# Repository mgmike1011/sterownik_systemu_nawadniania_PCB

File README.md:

# sterownik_systemu_nawadniania_PCB
Projekt płytki drukowanej sterownika systemu nawadaniania w oparciu o STM32

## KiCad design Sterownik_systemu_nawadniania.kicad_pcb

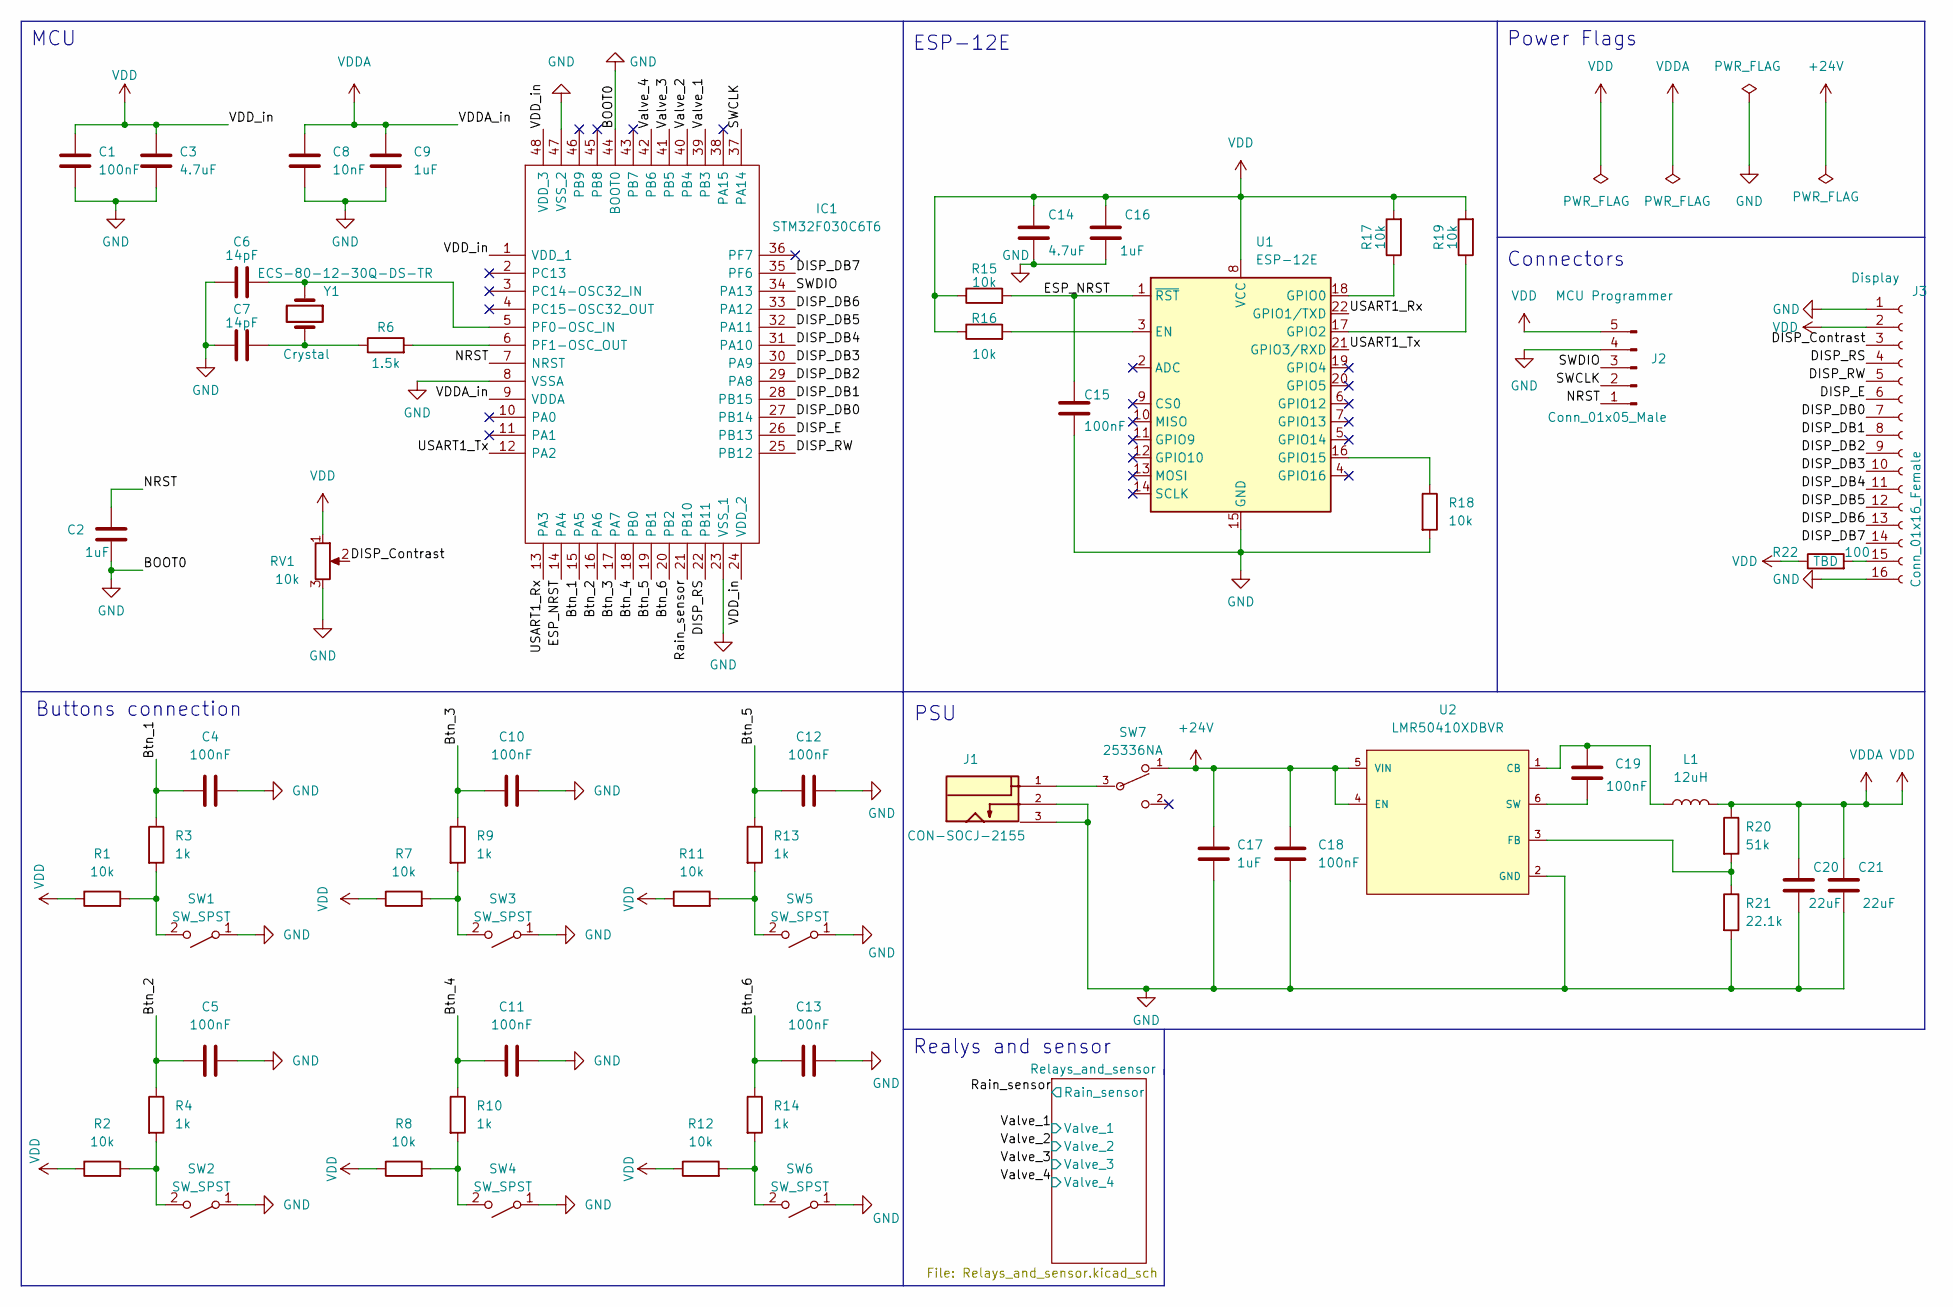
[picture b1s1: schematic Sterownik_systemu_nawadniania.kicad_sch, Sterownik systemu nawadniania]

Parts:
C1, C4, C5, C10, C11, C12, C13, C15, C18, C19: 100nF; C_0603_1608Metric
C2, C9, C16, C17: 1uF; C_0603_1608Metric
C3, C14: 4.7uF; C_0603_1608Metric
C6, C7: 14pF; C_0402_1005Metric
C8: 10nF; C_0603_1608Metric
C20, C21: 22uF; C_2220_5650Metric
IC1: STM32F030C6T6; QFP50P900X900X160-48N; Mouser Part Number 511-STM32F030C6T6
J1: CON-SOCJ-2155; GRAVITECH_CON-SOCJ-2155; PARTREV NA
J2: Conn_01x05_Male; PinHeader_1x05_P2.54mm_Vertical
J3: Conn_01x16_Female; PinSocket_1x16_P2.54mm_Vertical
L1: 12uH; RLB0712-120KL
R1, R2, R7, R8, R11, R12, R15, R16, R17, R18, R19: 10k; R_0603_1608Metric
R3, R4, R9, R10, R13, R14: 1k; R_0603_1608Metric
R6: 1.5k; R_0603_1608Metric
R20: 51k; R_0603_1608Metric
R21: 22.1k; R_0603_1608Metric
R22: 100; R_0603_1608Metric
RV1: 10k; TRIM_3362P-1-103LF
SW1, SW2, SW3, SW4, SW5, SW6: SW_SPST; 430156043736_AM
SW7: 25336NA; Apem_Inc.-25336NA-MFG; voltage rating DC 30V; mouser part number 642-25336NA; digikey description SWITCH SLIDE SPDT 4A 125V
U1: ESP-12E
U2: LMR50410XDBVR; Texas_Instruments-DBV0006A-0-0-MFG; output voltage 1-28V; mouser part number 595-LMR50410XDBVR; digikey description SIMPLE SWITCHER 4-V TO 36-V, 1-A
Y1: Crystal; XTAL_ECS-80-18-30-JGN-TR

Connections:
/Btn_1: C4.1, IC1.15 (PA5), R3.1
/Btn_2: C5.1, IC1.16 (PA6), R4.1
/Btn_3: C10.1, IC1.17 (PA7), R9.1
/Btn_4: C11.1, IC1.18 (PB0), R10.1
/Btn_5: C12.1, IC1.19 (PB1), R13.1
/Btn_6: C13.1, IC1.20 (PB2), R14.1
/DISP_Contrast: J3.3, RV1.2
/DISP_DB0: IC1.27 (PB14), J3.7
/DISP_DB1: IC1.28 (PB15), J3.8
/DISP_DB2: IC1.29 (PA8), J3.9
/DISP_DB3: IC1.30 (PA9), J3.10
/DISP_DB4: IC1.31 (PA10), J3.11
/DISP_DB5: IC1.32 (PA11), J3.12
/DISP_DB6: IC1.33 (PA12), J3.13
/DISP_DB7: IC1.35 (PF6), J3.14
/DISP_E: IC1.26 (PB13), J3.6
/DISP_RS: IC1.22 (PB11), J3.4
/DISP_RW: IC1.25 (PB12), J3.5
/ESP_NRST: C15.1, IC1.14 (PA4), R15.2, U1.1 (~RST)
/NRST: C2.1, IC1.7 (NRST), J2.1
/Rain_sensor: IC1.21 (PB10); also elsewhere on the board
/SWCLK: IC1.37 (PA14), J2.2
/SWDIO: IC1.34 (PA13), J2.3
/USART1_Rx: IC1.13 (PA3), U1.22 (GPIO1/TXD)
/USART1_Tx: IC1.12 (PA2), U1.21 (GPIO3/RXD)
/Valve_1: IC1.39 (PB3); also elsewhere on the board
/Valve_2: IC1.40 (PB4); also elsewhere on the board
/Valve_3: IC1.41 (PB5); also elsewhere on the board
/Valve_4: IC1.42 (PB6); also elsewhere on the board
GND: C1.2, C2.2, C3.2, C4.2, C5.2, C6.1, C7.1, C8.2, C9.2, C10.2, C11.2, C12.2, C13.2, C14.2, C15.2, C16.2, C17.2, C18.2, C20.2, C21.2, IC1.8 (VSSA), IC1.23 (VSS_1), IC1.44 (BOOT0), IC1.47 (VSS_2), J1.2, J1.3, J2.4, J3.1, J3.16, R18.2, R21.2, RV1.3, SW1.1 (A), SW2.1 (A), SW3.1 (A), SW4.1 (A), SW5.1 (A), SW6.1 (A), U1.15 (GND), U2.2 (GND); also elsewhere on the board
unnamed: C6.2, IC1.5 (PF0-OSC_IN), Y1.1
unnamed: C7.2, R6.1, Y1.2
unnamed: C19.1, L1.1, U2.1 (CB)
unnamed: C19.2, U2.6 (SW)
unnamed: IC1.6 (PF1-OSC_OUT), R6.2
unnamed: J1.1, SW7.3 (Common)
unnamed: J3.15, R22.2
unnamed: R1.2, R3.2, SW1.2 (B)
unnamed: R2.2, R4.2, SW2.2 (B)
unnamed: R7.2, R9.2, SW3.2 (B)
unnamed: R8.2, R10.2, SW4.2 (B)
unnamed: R11.2, R13.2, SW5.2 (B)
unnamed: R12.2, R14.2, SW6.2 (B)
unnamed: R16.2, U1.3 (EN)
unnamed: R17.1, U1.18 (GPIO0)
unnamed: R18.1, U1.16 (GPIO15)
unnamed: R19.1, U1.17 (GPIO2)
unnamed: R20.2, R21.1, U2.3 (FB)
VDD: C1.1, C3.1, C8.1, C9.1, C14.1, C16.1, C20.1, C21.1, IC1.1 (VDD_1), IC1.9 (VDDA), IC1.24 (VDD_2), IC1.48 (VDD_3), J2.5, J3.2, L1.2, R1.1, R2.1, R7.1, R8.1, R11.1, R12.1, R15.1, R16.1, R17.2, R19.2, R20.1, R22.1, RV1.1, U1.8 (VCC); also elsewhere on the board

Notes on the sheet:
Realys and sensor
PSU
MCU
Buttons connection
Connectors
ESP-12E
Power Flags

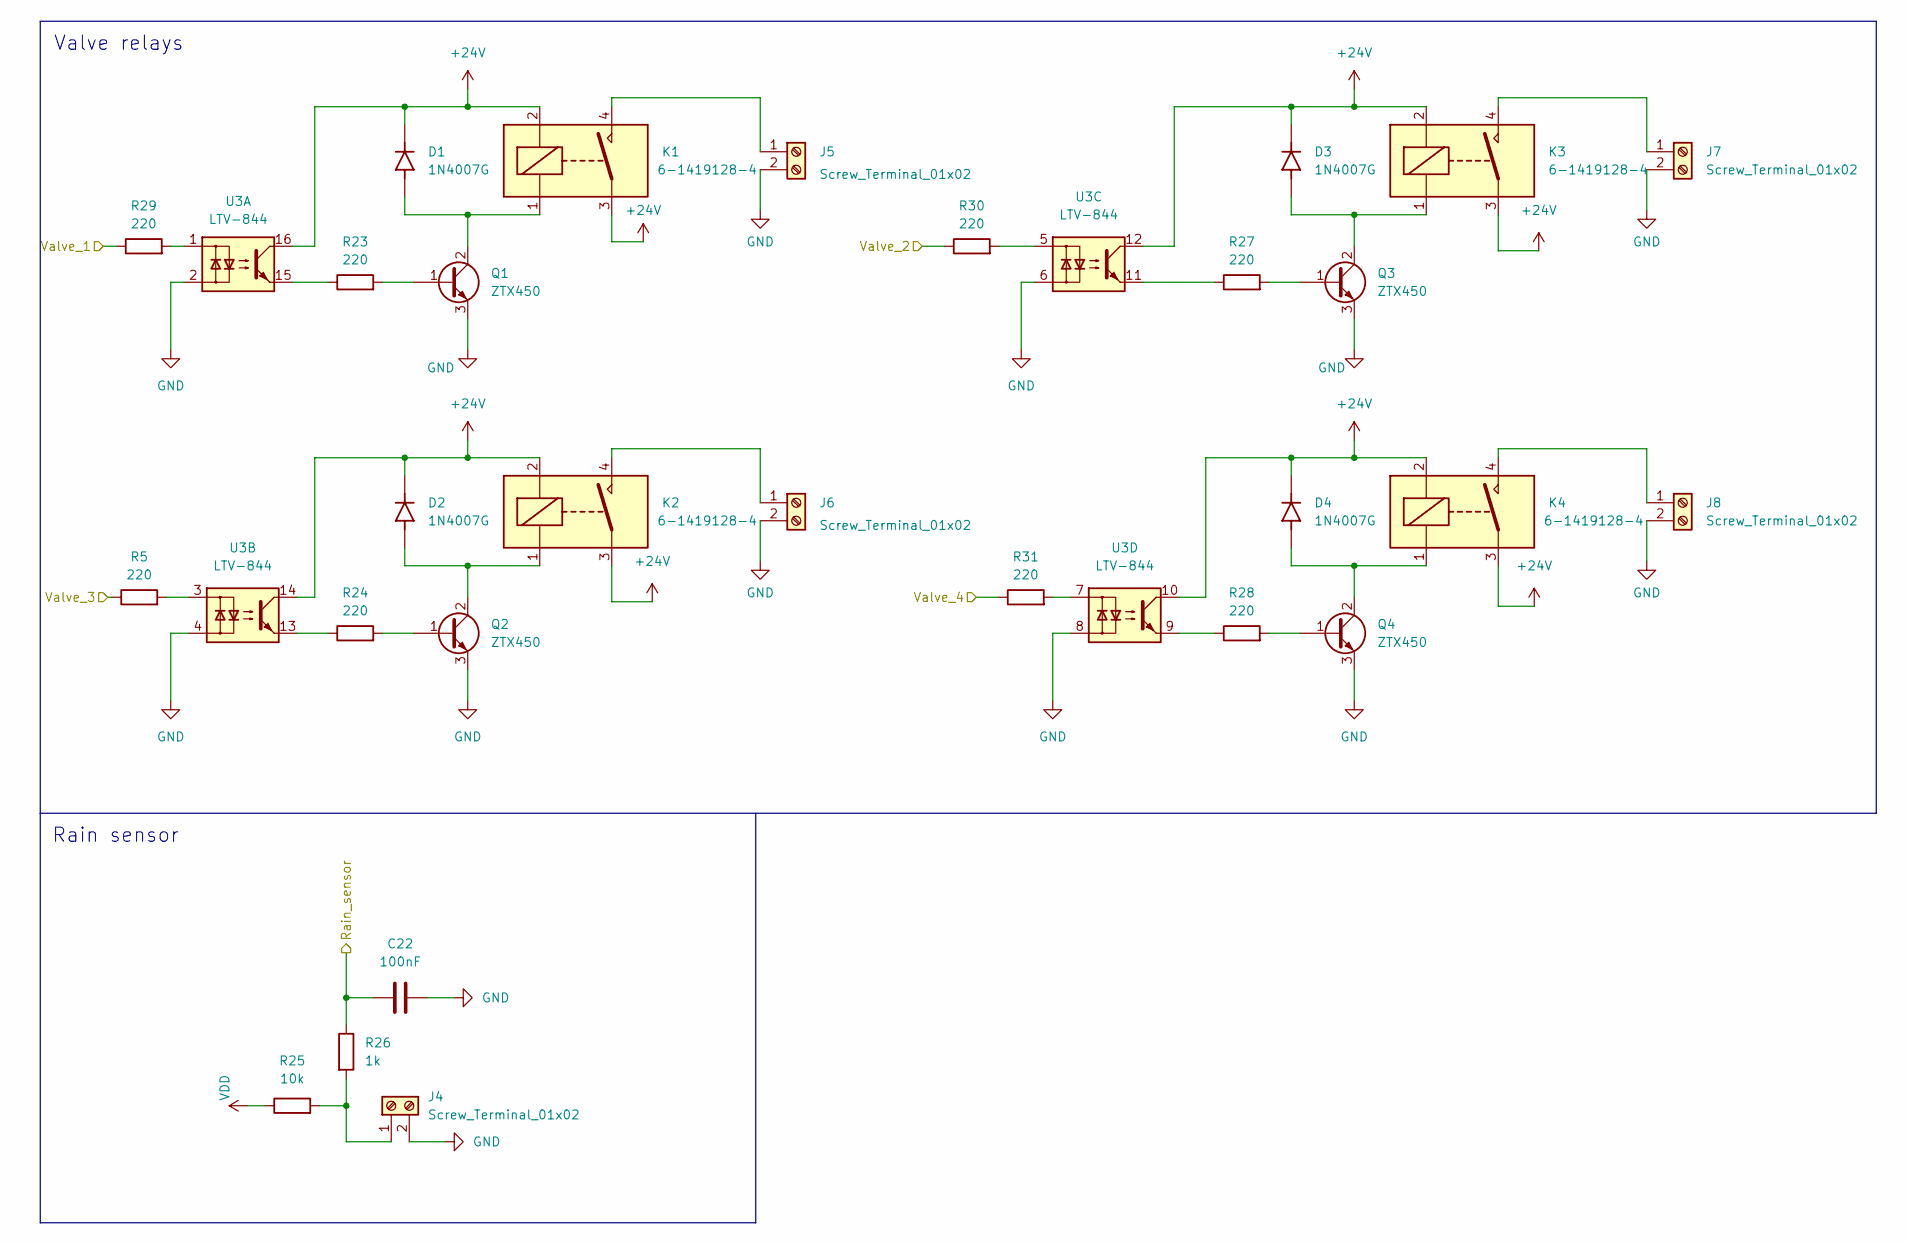
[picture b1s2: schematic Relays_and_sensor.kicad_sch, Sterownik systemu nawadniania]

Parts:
C22: 100nF; C_0603_1608Metric
D1, D2, D3, D4: 1N4007G; DIOAD1036W78L470D235; PARTREV P2104
J4, J5, J6, J7, J8: Screw_Terminal_01x02; TerminalBlock_bornier-2_P5.08mm
K1, K2, K3, K4: 6-1419128-4; OJ_OJE
Q1, Q2, Q3, Q4: ZTX450; TO92250P510H770-3
R5, R23, R24, R27, R28, R29, R30, R31: 220; R_0603_1608Metric
R25: 10k; R_0603_1608Metric
R26: 1k; R_0603_1608Metric
U3: LTV-844; DIP-16_W7.62mm

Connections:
/Rain_sensor: C22.1, R26.1; also elsewhere on the board
/Valve_1: R29.1; also elsewhere on the board
/Valve_2: R30.1; also elsewhere on the board
/Valve_3: R5.1; also elsewhere on the board
/Valve_4: R31.1; also elsewhere on the board
GND: C22.2, J4.2, J5.2, J6.2, J7.2, J8.2, Q1.3 (E), Q2.3 (E), Q3.3 (E), Q4.3 (E), U3.2, U3.4, U3.6, U3.8; also elsewhere on the board
unnamed: D1.A, K1.1, Q1.2 (C)
unnamed: D2.A, K2.1, Q2.2 (C)
unnamed: D3.A, K3.1, Q3.2 (C)
unnamed: D4.A, K4.1, Q4.2 (C)
unnamed: J4.1, R25.2, R26.2
unnamed: J5.1, K1.4
unnamed: J6.1, K2.4
unnamed: J7.1, K3.4
unnamed: J8.1, K4.4
unnamed: Q1.1 (B), R23.2
unnamed: Q2.1 (B), R24.2
unnamed: Q3.1 (B), R27.2
unnamed: Q4.1 (B), R28.2
unnamed: R5.2, U3.3
unnamed: R23.1, U3.15
unnamed: R24.1, U3.13
unnamed: R27.1, U3.11
unnamed: R28.1, U3.9
unnamed: R29.2, U3.1
unnamed: R30.2, U3.5
unnamed: R31.2, U3.7
VDD: R25.1; also elsewhere on the board

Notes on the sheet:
Rain sensor
Valve relays

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
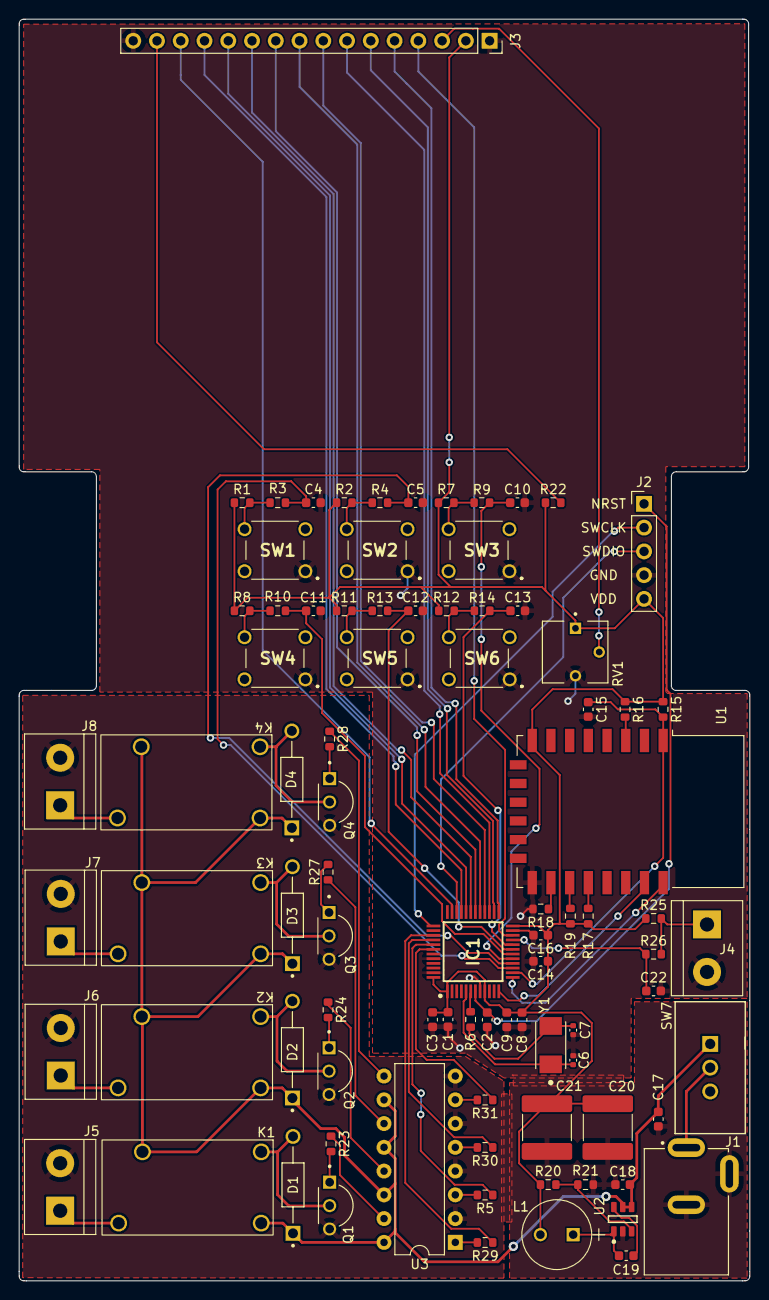
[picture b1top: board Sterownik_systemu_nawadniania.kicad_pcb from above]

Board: 2 copper layers, 78.1 x 134.9 mm, 87 parts (0 on the bottom side), 71 nets.

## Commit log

2022-10-28 Init
2022-10-28 Lib folder added
2022-10-28 Page setup
2022-11-04 MCU + ESP
2022-11-05 Connectors
2022-11-05 6 buttons with RC filters
2022-11-06 power unit
2022-11-06 Rain sensor
2022-11-06 ver 0.1
2022-11-07 Lab 07.11
2022-11-08 Isolation
2022-11-10 Rezystory, kondensatory, cewka - footprints
2022-11-10 footprints
2022-11-11 group
2022-11-14 lab 14.11
2022-11-14 stable1
2022-11-17 Routing with ground field
2022-11-21 Lab 21.11
2022-11-21 PCB update
2022-11-27 Routing and keep out zones
2022-12-05 lab 14:40
2022-12-15 final

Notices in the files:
parts and their libraries:
Copyright 2021 Accelerated Designs. All rights reserved.
